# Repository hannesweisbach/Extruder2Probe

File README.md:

# Extruder2Probe
Board in stepstick formfactor to attach a PINDA v2 Probe to an empty extruder port

This is part of the modifications of my Sapphire Pro. I wanted to connect a PINDA v2 Z-probe (with temperature sensor). The Sapphire Pro is controlled by an MKS Robin Nano board. 

## Why?
The board has a BLTouch connector, which I could have used, where it not for two issues:

1. my board runs on 3.3V, so it does not have 5V readily available, which the PINDA v2 needs and
2. the BLTouch connector does not connect the temperature sensor of the probe.

## How?

I do, however, use only one extruder, which means the socket for the E1 stepper driver board is empty. This means I have:

* a 4-pin connector for the probe (5V, GND, Signal, Temperature)
* 24V at the stepstick board to generate 5V for the probe
* space to invert the probe signal
* space to condition the analog signal.

The STEP pin on the socket is connected to pin PA6 of the STM23F103 SoC, the DIR pin to pin PA1. PA1 can also be an analog input, hence the temperature sensor has to be connected to this pin.

## Details?

The `EDA` subdirectory contains schematic and board layout in KiCAD format, as well as a [PDF version of the schematic](https://github.com/hannesweisbach/Extruder2Probe/raw/main/EDA/Probe%20Connector.pdf).

Q1 can either be a BJT or MOSFET. R5 is required if Q1 is a BJT, but optional if Q1 is a FET. D2 in conjunction with R5 keeps the gate voltage of Q1 within 0-5V and also acts as a (rudimentary) ESD protection.

## Pictures?

3D rendering of the board:

Board mounted on the MKS Robin Nano:

With probe attached:

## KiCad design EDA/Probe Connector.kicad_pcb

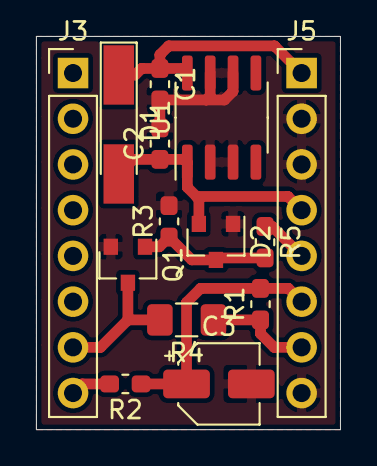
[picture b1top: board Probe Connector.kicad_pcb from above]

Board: 2 copper layers, 16.9 x 21.8 mm, 14 parts (0 on the bottom side), 9 nets.

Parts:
C1, C2: 100n; C_0603_1608Metric_Pad1.05x0.95mm_HandSolder
C3: 10u; CP_Elec_4x5.7
D1: D; D_MiniMELF_Handsoldering
D2: BAT54S; SOT-23
J3, J5: Conn_01x08; PinHeader_1x08_P2.54mm_Vertical
Q1: BSS138; SOT-23
R1: 4k7; R_0603_1608Metric_Pad1.05x0.95mm_HandSolder
R2: 100; R_0603_1608Metric_Pad1.05x0.95mm_HandSolder
R3: 10k; R_0603_1608Metric_Pad1.05x0.95mm_HandSolder
R4: 10k; R_1206_3216Metric_Pad1.42x1.75mm_HandSolder
R5: 1k; R_0603_1608Metric_Pad1.05x0.95mm_HandSolder
U1: LM78L05_SO8; SOIC-8_3.9x4.9mm_P1.27mm

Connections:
+3V3: J5.7, R1.1, R4.1
+5V: C2.1, D1.2, D2.2, J5.4, U1.1
+24V: C1.1, D1.1, J5.1, U1.8
GND: C1.2, C2.2, C3.2, D2.1, J5.2, J5.3, J5.8, Q1.2, R3.2, U1.2, U1.3, U1.6, U1.7
unnamed: C3.1, R1.2, R2.1
unnamed: D2.3, Q1.1, R3.1, R5.2
unnamed: J3.7, Q1.3, R4.2
unnamed: J3.8, R2.2
unnamed: J5.5, R5.1

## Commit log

2021-05-31 Add description to README
2021-05-31 Add EDA files
2021-05-31 Add Schematic PDF
2021-05-31 Add link to schematic PDF
2021-05-31 Add pictures
2021-05-31 Add explanation of schematic and structure
2021-05-31 Fix typo in README.md
